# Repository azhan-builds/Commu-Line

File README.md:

# Commu Line

This project aims to solve a problem related to disaster situations. During disasters, the network and communication infrastructure often breaks down, leading to loss of proper communication between people especially rescuers. For V1, I am trying to focus only on the communication between rescue teams.

I will be developing a LoRa mesh communication node for disaster zones. I will be developing small pods that will be placed in a defined distance to create a mesh network.

## What it does

A pod is a small standalone node. They will dropped around an affected area in order to create or form a mesh network.

Each pod:
- Relays text messages hop to hop, so range is not limited to one node's radio.
- It can also run a local Wifi hotspot so any phone can connect to it and send an SOS message without needing an app.
- It will also feature a physical SOS button in case phone isn't an option.
- It will log GPS positions and status.
- Stores and forwards messages if the network is broken mid-hop.

For V1, we hope to develop 7 pods.

## Hardware

- ESP32-S3 dev board for computing
- Waveshare Core1262-HF module (SX1262 LoRa radio, IN865 band)
- Neo-6 GPS
- 0.96' Oled display
- TP4056 charger + single-cell Li-ion battery
- SOS button, buzzer and status LEDs
- PVC enclosure (For prototyping, PVC will be used but once the system is up and running, we will shift to 3d printing.)
- Circuit on a vero board (Custom PCB will be developed only after the system is ready)

I will not be using any pre-integrated boards like Heltec or seeed. Radio and compute are seperate and will be wired and programmed by me.

## Status

V1 scope: text mesh only (discovery, multi-hop, store-and-forward, ACK, local wifi UI).

Image transfer will be experimental. Survivor to rescue teams is planned for V2.

So far the hardware is finalised. The next step is schematics.

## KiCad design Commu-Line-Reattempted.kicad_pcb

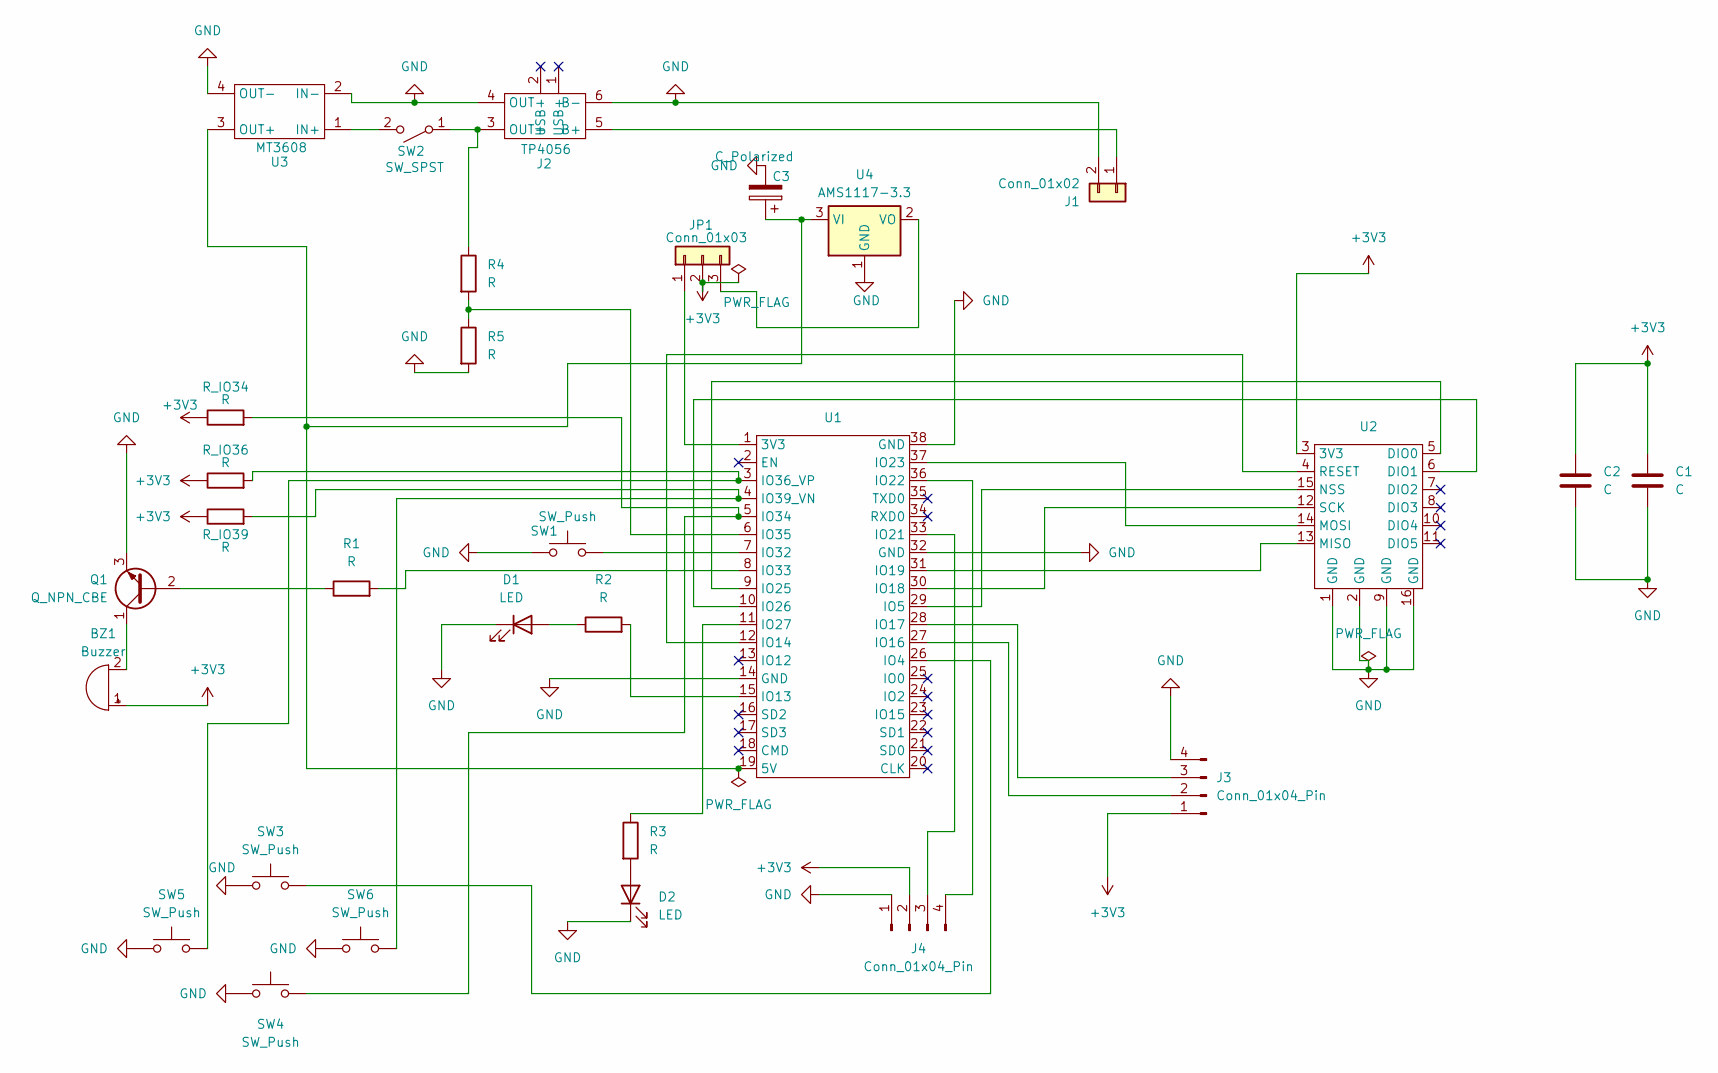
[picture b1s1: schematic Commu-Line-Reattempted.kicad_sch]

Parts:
BZ1: Buzzer; Buzzer_12x9.5RM7.6
C1: C; C_Disc_D5.0mm_W2.5mm_P5.00mm
C2: C; CP_Radial_D6.3mm_P2.50mm
C3: C_Polarized; CP_Radial_D6.3mm_P2.50mm
D1, D2: LED; LED_D5.0mm
J1: Conn_01x02; JST_XH_B2B-XH-A_1x02_P2.50mm_Vertical
J2: TP4056; TP4056-18650
J3, J4: Conn_01x04_Pin; PinSocket_1x04_P2.54mm_Vertical
JP1: Conn_01x03; PinHeader_1x03_P2.54mm_Vertical
Q1: Q_NPN_CBE; TO-92_Inline
R1, R2, R3, R4, R5: R; R_Axial_DIN0207_L6.3mm_D2.5mm_P7.62mm_Horizontal
R_IO34, R_IO36, R_IO39: R; R_Axial_DIN0207_L6.3mm_D2.5mm_P7.62mm_Horizontal
SW1: SW_Push; JST_XH_B2B-XH-A_1x02_P2.50mm_Vertical
SW2: SW_SPST; JST_XH_B2B-XH-A_1x02_P2.50mm_Vertical
SW3, SW4, SW5, SW6: SW_Push; SW_PUSH_6mm
U1: ESP32_DevKit_38pin_W25.4mm
U2: Ra02_Breakout_2x8_W25.4mm
U3: MT3608; MT3608_Module_v2
U4: AMS1117-3.3; SOT-223-3_TabPin2

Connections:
+3V3: BZ1.1 (+), C1.2, C2.1, J3.1, J4.2, JP1.2, R_IO34.1, R_IO36.1, R_IO39.1, U2.3 (3V3)
GND: C1.1, C2.2, C3.2, D1.1 (K), D2.1 (K), J1.2, J2.4 (OUT-), J2.6 (B-), J3.4, J4.1, Q1.3 (E), R5.2, SW1.1, SW3.1, SW4.1, SW5.1, SW6.1, U1.14 (GND), U1.32 (GND), U1.38 (GND), U2.1 (GND), U2.2 (GND), U2.9 (GND), U2.16 (GND), U3.2 (IN-), U3.4 (OUT-), U4.1 (GND)
unnamed: BZ1.2 (-), Q1.1 (C)
unnamed: D1.2 (A), R2.1
unnamed: D2.2 (A), R3.2
unnamed: J1.1, J2.5 (B+)
unnamed: J2.3 (OUT+), R4.1, SW2.1 (A)
unnamed: J3.2, U1.27 (IO16)
unnamed: J3.3, U1.28 (IO17)
unnamed: J4.3, U1.33 (IO21)
unnamed: J4.4, U1.36 (IO22)
unnamed: JP1.1, U1.1 (3V3)
unnamed: JP1.3, U4.2 (VO)
unnamed: Q1.2 (B), R1.1
unnamed: SW2.2 (B), U3.1 (IN+)
unnamed: C3.1, U1.19 (5V), U3.3 (OUT+), U4.3 (VI)
unnamed: SW3.2, U1.26 (IO4)
unnamed: U1.29 (IO5), U2.15 (NSS)
unnamed: R2.2, U1.15 (IO13)
unnamed: U1.12 (IO14), U2.4 (RESET)
unnamed: U1.30 (IO18), U2.12 (SCK)
unnamed: U1.31 (IO19), U2.13 (MISO)
unnamed: U1.37 (IO23), U2.14 (MOSI)
unnamed: U1.9 (IO25), U2.5 (DIO0)
unnamed: U1.10 (IO26), U2.6 (DIO1)
unnamed: R3.1, U1.11 (IO27)
unnamed: SW1.2, U1.7 (IO32)
unnamed: R1.2, U1.8 (IO33)
unnamed: R_IO34.2, SW4.2, U1.5 (IO34)
unnamed: R4.2, R5.1, U1.6 (IO35)
unnamed: R_IO36.2, SW5.2, U1.3 (IO36_VP)
unnamed: R_IO39.2, SW6.2, U1.4 (IO39_VN)

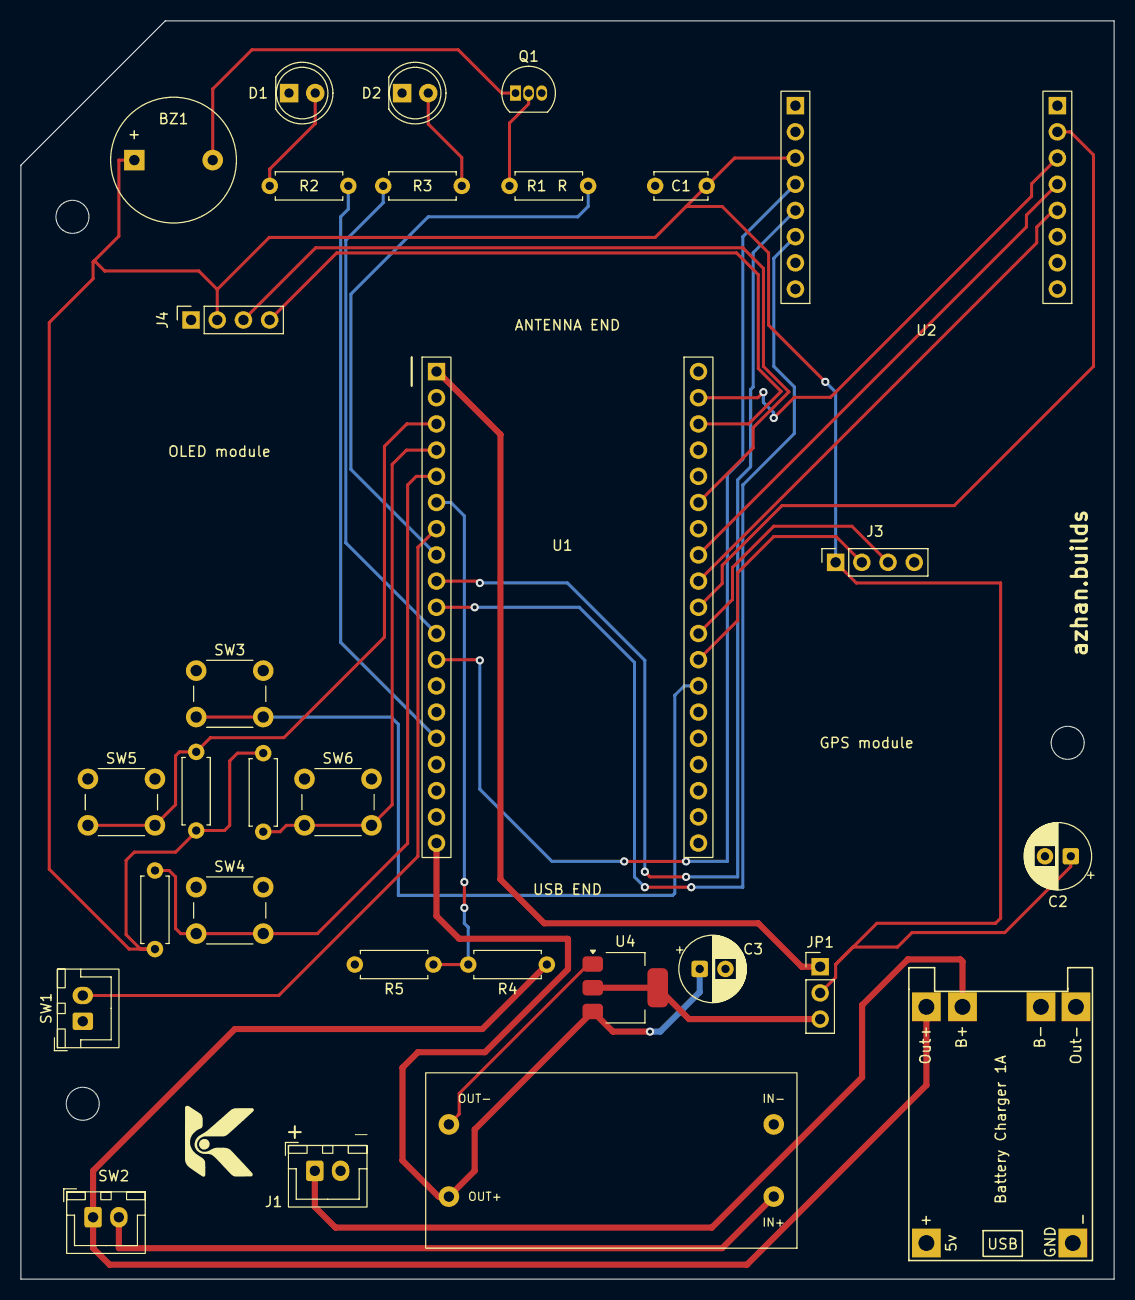
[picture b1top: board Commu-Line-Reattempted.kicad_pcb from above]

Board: 2 copper layers, 106.0 x 122.0 mm, 30 parts (0 on the bottom side), 32 nets.
